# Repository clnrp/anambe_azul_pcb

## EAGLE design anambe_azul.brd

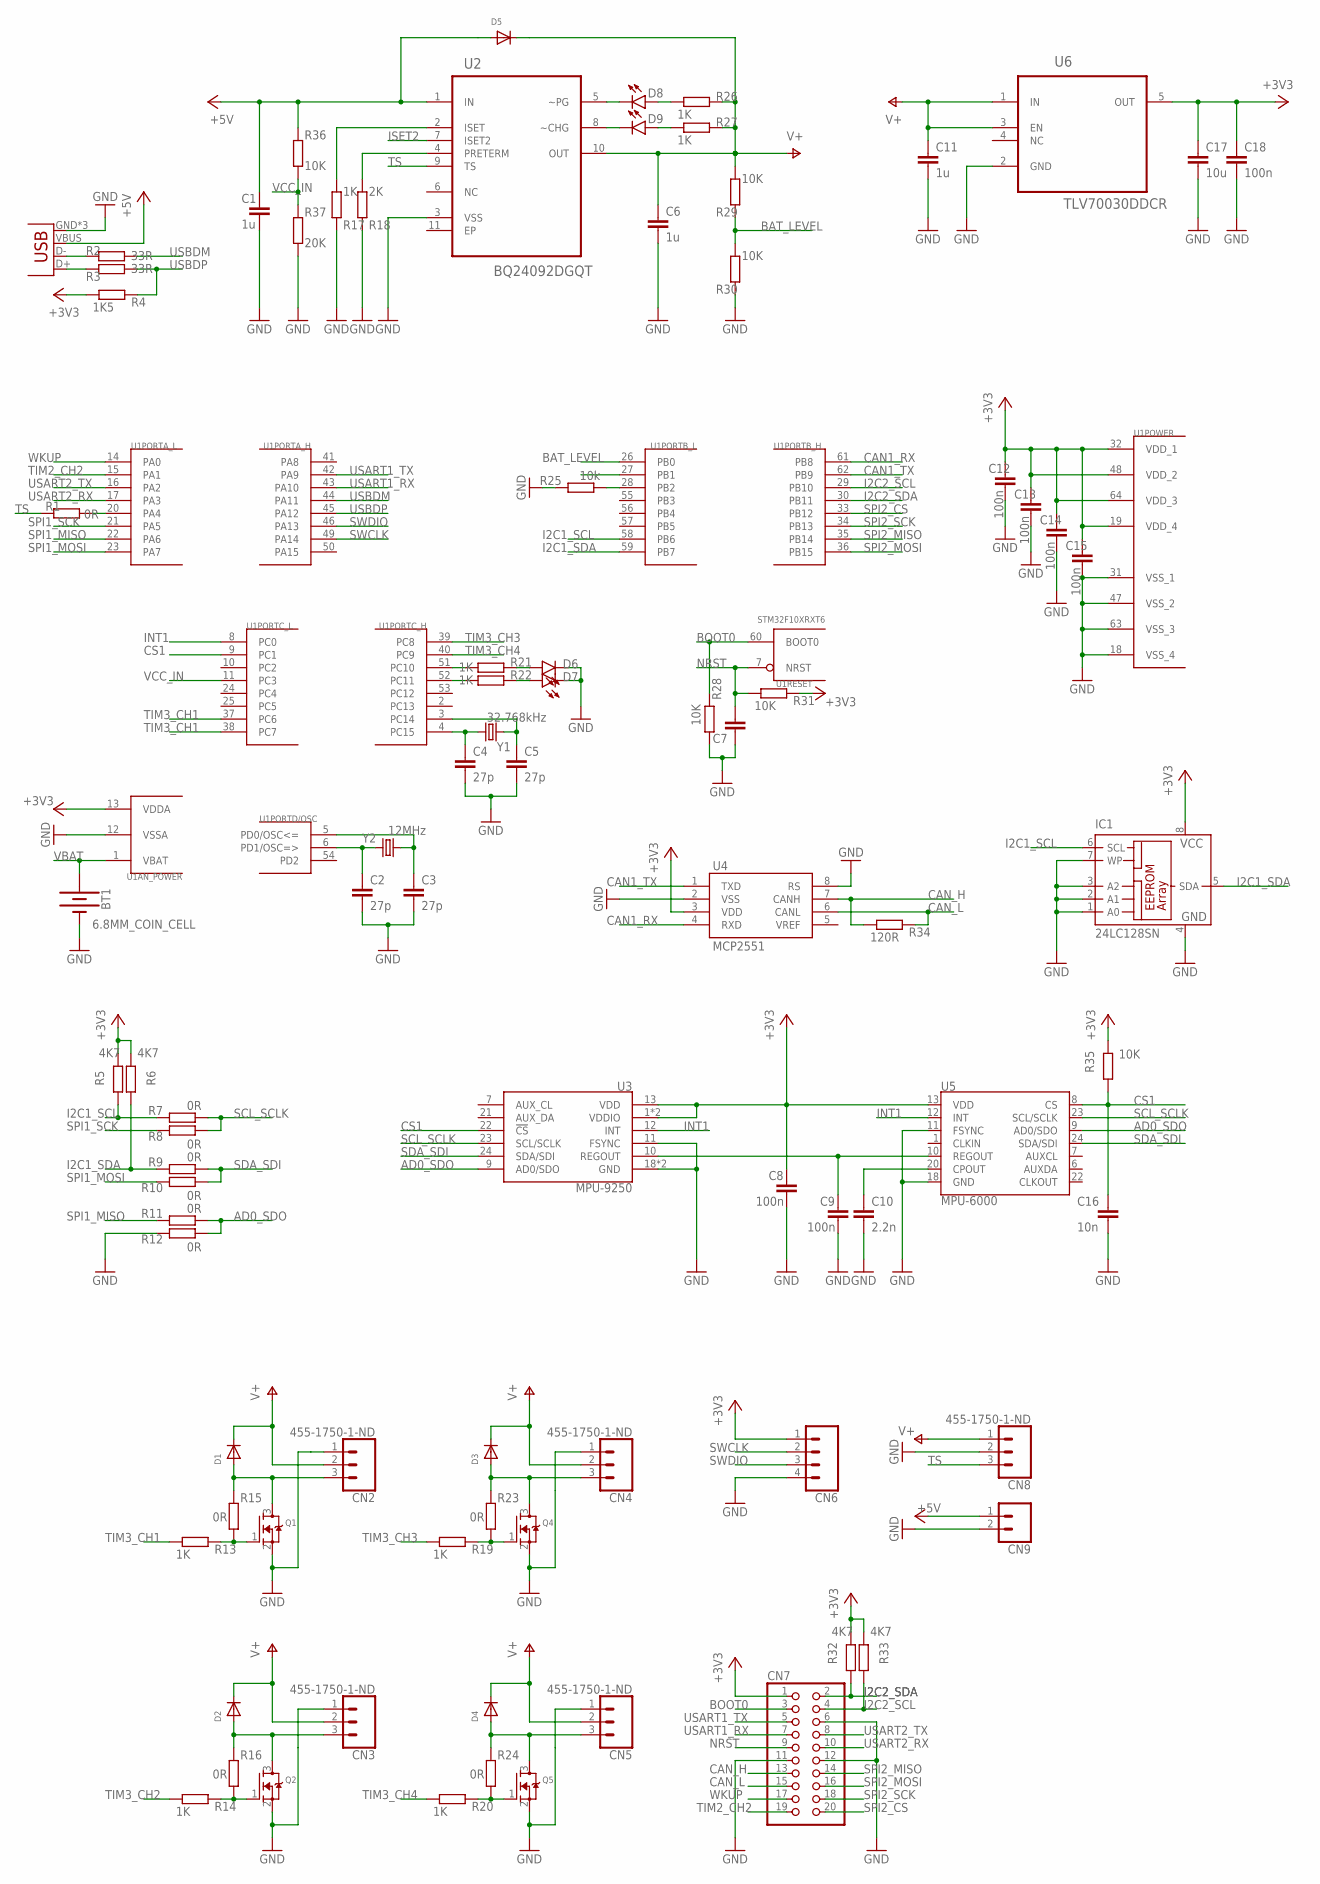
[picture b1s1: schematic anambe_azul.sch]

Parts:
BT1: 6.8MM_COIN_CELL; BATTCON-6.8MM
C1, C6, C11: 1u; C0603
C2, C3, C4, C5: 27p; C0603
C7: C-EUC0603; C0603
C8, C9, C12, C13, C14, C15, C18: 100n; C0603
C10: 2.2n; C0603
C16: 10n; C0603
C17: 10u; C0603
CN1: SPARKFUN-CONNECTORS_USB-MICROB
CN2, CN3, CN4, CN5, CN8: 455-1750-1-ND; 1X03
CN6: CONN_04; 1X04
CN7: PINHD-2X10; 2X10
CN9: CONN_02; 1X02
D1, D2, D3, D4, D5: DIODESOD-123; SOD-123
D6, D7, D8, D9: LED0603; LED-0603
IC1: 24LC128SN; SO-08
Q1, Q2, Q4, Q5: MOSFET-NREFLOW; SOT23
R1, R7, R8, R9, R10, R11, R12, R15, R16, R23, R24: 0R; R0603
R2, R3: 33R; R0603
R4: 1K5; R0603
R5, R6, R32, R33: 4K7; R0603
R13, R14, R17, R19, R20, R21, R22, R26, R27: 1K; R0603
R18: 2K; R0603
R25: 10k; R0603
R28, R29, R30, R31, R35, R36: 10K; R0603
R34: 120R; R0603
R37: 20K; R0603
U1: STM32F10XRXT6; TQFP64
U2: BQ24092DGQT; SOP50P490X110-11N
U3: MPU-9250; QFN24-3X3
U4: MCP2551; SO08
U5: MPU-6000; QFN-24-EP
U6: TLV70030DDCR; SOT95P280X110-5N
Y1: 32.768kHz; CRYSTAL-PTH-2X6-CYL
Y2: 12MHz; HC49UP

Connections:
+3V3: C8.1, C12.1, C13.1, C14.1, C15.1, C17.1, C18.1, CN6.1, CN7.1, IC1.8 (VCC), R4.1, R5.1, R6.1, R31.2, R32.1, R33.1, R35.2, U1.13 (VDDA), U1.19 (VDD_4), U1.32 (VDD_1), U1.48 (VDD_2), U1.64 (VDD_3), U3.1 (VDDIO), U3.8 (VDDIO), U3.13 (VDD), U4.3 (VDD), U5.13 (VDD), U6.5 (OUT)
+5V: C1.1, CN1.VBUS, CN9.1, D5.A, R36.2, U2.1 (IN)
AD0_SDO: R11.1, R12.1, U3.9 (AD0/SDO), U5.9 (AD0/SDO)
BAT_LEVEL: R29.2, R30.1, U1.26 (PB0)
BOOT0: CN7.3, R28.2, U1.60 (BOOT0)
CAN1_RX: U1.61 (PB8), U4.4 (RXD)
CAN1_TX: U1.62 (PB9), U4.1 (TXD)
CAN_H: CN7.13, R34.1, U4.7 (CANH)
CAN_L: CN7.15, R34.2, U4.6 (CANL)
CS1: C16.1, R35.1, U1.9 (PC1), U3.22 (!CS), U5.8 (CS)
GND: BT1.-, C1.2, C2.2, C3.2, C4.2, C5.2, C6.2, C7.1, C8.2, C9.2, C10.2, C11.2, C12.2, C13.2, C14.2, C15.2, C16.2, C17.2, C18.2, CN1.GND, CN1.MT1 (GND), CN1.MT2 (GND), CN2.1, CN3.1, CN4.1, CN5.1, CN6.4, CN7.6, CN7.11, CN7.12, CN8.2, CN9.2, D6.C, D7.C, IC1.1 (A0), IC1.2 (A1), IC1.3 (A2), IC1.4 (GND), IC1.7 (WP), Q1.2 (S), Q2.2 (S), Q4.2 (S), Q5.2 (S), R12.2, R17.2, R18.2, R25.2, R28.1, R30.2, R37.2, U1.12 (VSSA), U1.18 (VSS_4), U1.31 (VSS_1), U1.47 (VSS_2), U1.63 (VSS_3), U2.3 (VSS), U3.11 (FSYNC), U3.18 (GND), U3.20 (GND), U4.2 (VSS), U4.8 (RS), U5.11 (FSYNC), U5.18 (GND), U6.2 (GND)
I2C1_SCL: IC1.6 (SCL), R5.2, R7.2, U1.58 (PB6)
I2C1_SDA: IC1.5 (SDA), R6.2, R9.2, U1.59 (PB7)
I2C2_SCL: CN7.4, R33.2, U1.29 (PB10)
I2C2_SDA: CN7.2, R32.2, U1.30 (PB11)
INT1: U1.8 (PC0), U3.12 (INT), U5.12 (INT)
ISET2: U1.27 (PB1), U2.7 (ISET2)
unnamed: C2.1, U1.6 (PD1/OSC=>), Y2.1
unnamed: CN1.D+, R3.1
unnamed: C3.1, U1.5 (PD0/OSC<=), Y2.2
unnamed: Q1.1 (G), R13.2, R15.1
unnamed: CN1.D-, R2.1
unnamed: C4.1, U1.4 (PC15), Y1.2
unnamed: C5.1, U1.3 (PC14), Y1.1
unnamed: CN2.3, D1.A, Q1.3 (D), R15.2
unnamed: Q4.1 (G), R19.2, R23.1
unnamed: CN4.3, D3.A, Q4.3 (D), R23.2
unnamed: Q2.1 (G), R14.2, R16.1
unnamed: C10.1, U5.20 (CPOUT)
unnamed: C9.1, U3.10 (REGOUT), U5.10 (REGOUT)
unnamed: D9.C, U2.8 (~CHG)
unnamed: CN3.3, D2.A, Q2.3 (D), R16.2
unnamed: Q5.1 (G), R20.2, R24.1
unnamed: CN5.3, D4.A, Q5.3 (D), R24.2
unnamed: R25.1, U1.28 (PB2)
unnamed: D9.A, R27.1
unnamed: D8.A, R26.1
unnamed: D8.C, U2.5 (~PG)
unnamed: R17.1, U2.2 (ISET)
unnamed: R18.1, U2.4 (PRETERM)
unnamed: R21.1, U1.51 (PC10)
unnamed: R22.1, U1.52 (PC11)
unnamed: D6.A, R21.2
unnamed: D7.A, R22.2
unnamed: R1.1, U1.20 (PA4)
NRST: C7.2, CN7.9, R31.1, U1.7 (NRST)
SCL_SCLK: R7.1, R8.1, U3.23 (SCL/SCLK), U5.23 (SCL/SCLK)
SDA_SDI: R9.1, R10.1, U3.24 (SDA/SDI), U5.24 (SDA/SDI)
SPI1_MISO: R11.2, U1.22 (PA6)
SPI1_MOSI: R10.2, U1.23 (PA7)
SPI1_SCK: R8.2, U1.21 (PA5)
SPI2_CS: CN7.20, U1.33 (PB12)
SPI2_MISO: CN7.14, U1.35 (PB14)
SPI2_MOSI: CN7.16, U1.36 (PB15)
SPI2_SCK: CN7.18, U1.34 (PB13)
SWCLK: CN6.2, U1.49 (PA14)
SWDIO: CN6.3, U1.46 (PA13)
TIM2_CH2: CN7.19, U1.15 (PA1)
TIM3_CH1: R13.1, U1.37 (PC6)
TIM3_CH2: R14.1, U1.38 (PC7)
TIM3_CH3: R19.1, U1.39 (PC8)
TIM3_CH4: R20.1, U1.40 (PC9)
TS: CN8.3, R1.2, U2.9 (TS)
USART1_RX: CN7.7, U1.43 (PA10)
USART1_TX: CN7.5, U1.42 (PA9)
USART2_RX: CN7.10, U1.17 (PA3)
USART2_TX: CN7.8, U1.16 (PA2)
USBDM: R2.2, U1.44 (PA11)
USBDP: R3.2, R4.2, U1.45 (PA12)
V+: C6.1, C11.1, CN2.2, CN3.2, CN4.2, CN5.2, CN8.1, D1.C, D2.C, D3.C, D4.C, D5.C, R26.2, R27.2, R29.1, U2.10 (OUT), U6.1 (IN), U6.3 (EN)
VBAT: BT1.+, U1.1 (VBAT)
VCC_IN: R36.1, R37.1, U1.11 (PC3)
WKUP: CN7.17, U1.14 (PA0)

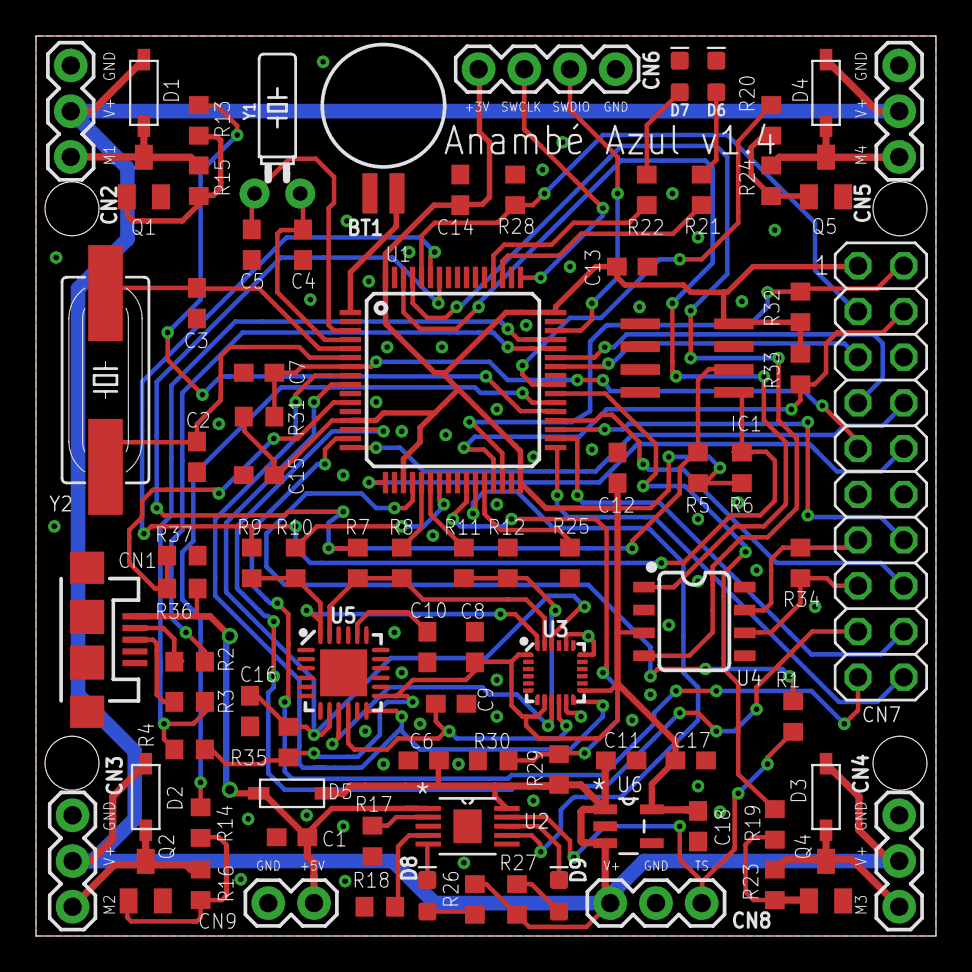
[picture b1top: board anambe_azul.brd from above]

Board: 2 copper layers, 50.0 x 50.0 mm, 87 parts (0 on the bottom side), 73 nets.

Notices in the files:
parts and their libraries:
SparkFun-Sensors: Licensing: Creative Commons ShareAlike 4.0 International - https://creativecommons.org/licenses/by-sa/4.0
